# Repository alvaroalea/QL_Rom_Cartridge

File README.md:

# QL_Rom_Cartridge
Schematic, PCB and other stuff to make ROM Cartridge for use with Sinclair QL Computer

(C) 2022 Alvaro Alea Fdz.

License under: CERN Open Hardware Licence Version 2 - Strongly Reciprocal

https://ohwr.org/cern_ohl_s_v2.txt

Remenber that when using my jerber files with JLCPCB you shall mark the option to specify the Order Number (no cost) to avoid the text JLCJLCJLCJLC in the skilscreen.

## Folder: Original
This folder contain the schematic of the original Sinclair cartridge as far as i can get from pictures from internet.

It also contains 3D pieces to do vacum form of the case

STATUS
- Schematic - Working, tested and match the original, Thank You Chr$.
- Case - Design, Non tested

## Folder: Short

### NOT TESTED, SHOULD WORK
This version need a 16Kb eprom, and is intended as a replacement of Toolkit II cartridge an others.

## Folder: full_rom

### NOT TESTED, NO IDEA IF WORK
This version need a 64Kb eprom, and is intended to replace the internal ROM of the QL.

Is very important to remove the 2 ROM chips from the QL before use.

Be aware that this lock the rom cartridge, and the QL will not work without it.

## Folder: 8full_rom

### NOT TESTED, NO IDEA IF WORK
The 8full_rom is a version of full_rom with 3 switch to allow 8 diferent version of the ROM of the QL.

Is very important to remove the 2 ROM chips from the QL before use.

Be aware that this lock the rom cartridge, and the QL will not work without it.

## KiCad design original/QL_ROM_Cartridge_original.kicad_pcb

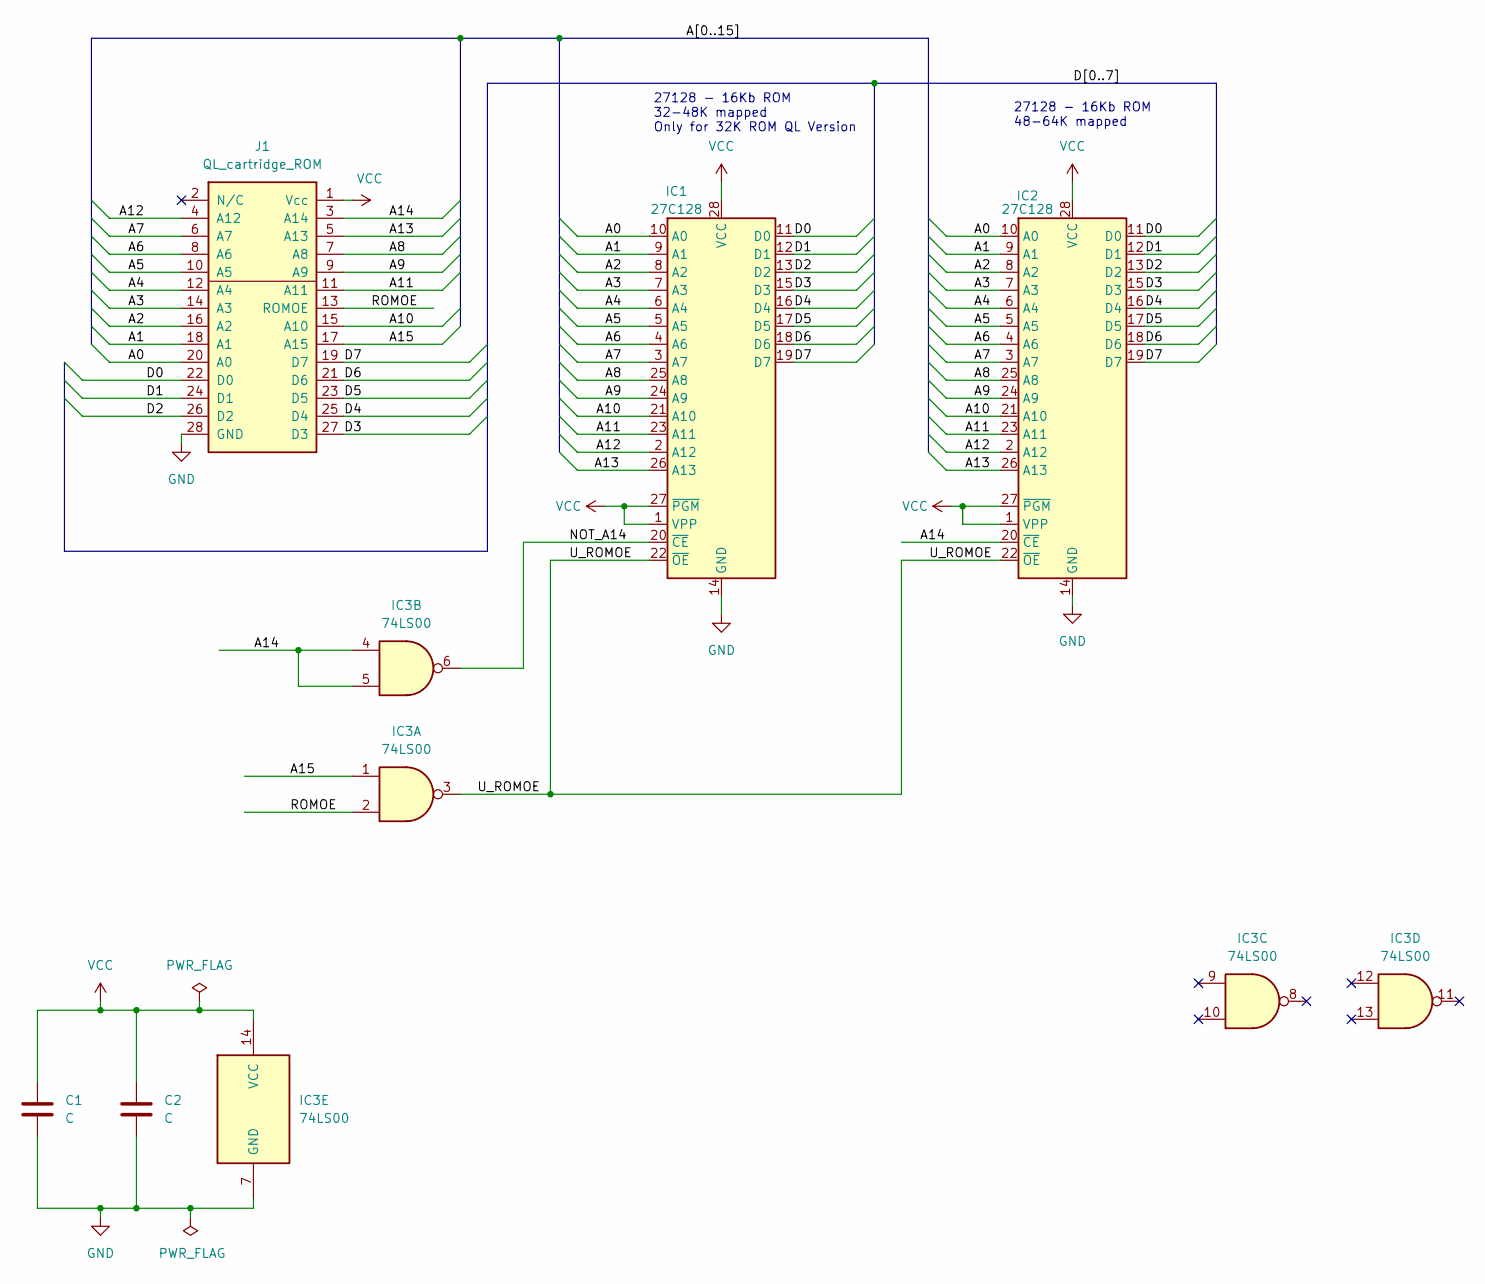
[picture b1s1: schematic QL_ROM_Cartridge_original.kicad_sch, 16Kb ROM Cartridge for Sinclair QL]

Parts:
C1: C; C_Axial_L3.8mm_D2.6mm_P12.50mm_Horizontal_Sinclair_Cartridge
C2: C; C_Axial_L3.8mm_D2.6mm_P12.50mm_Horizontal
IC1: 27C128; DIP-28_W15.24mm_sinclair_cartridge
IC2: 27C128; DIP-28_W15.24mm
IC3: 74LS00; DIP-14_W7.62mm
J1: QL_cartridge_ROM; CART_QL_EDGE

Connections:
/A0: IC1.10 (A0), IC2.10 (A0), J1.20 (A0)
/A1: IC1.9 (A1), IC2.9 (A1), J1.18 (A1)
/A2: IC1.8 (A2), IC2.8 (A2), J1.16 (A2)
/A3: IC1.7 (A3), IC2.7 (A3), J1.14 (A3)
/A4: IC1.6 (A4), IC2.6 (A4), J1.12 (A4)
/A5: IC1.5 (A5), IC2.5 (A5), J1.10 (A5)
/A6: IC1.4 (A6), IC2.4 (A6), J1.8 (A6)
/A7: IC1.3 (A7), IC2.3 (A7), J1.6 (A7)
/A8: IC1.25 (A8), IC2.25 (A8), J1.7 (A8)
/A9: IC1.24 (A9), IC2.24 (A9), J1.9 (A9)
/A10: IC1.21 (A10), IC2.21 (A10), J1.15 (A10)
/A11: IC1.23 (A11), IC2.23 (A11), J1.11 (A11)
/A12: IC1.2 (A12), IC2.2 (A12), J1.4 (A12)
/A13: IC1.26 (A13), IC2.26 (A13), J1.5 (A13)
/A14: IC2.20 (~CE), IC3.4, IC3.5, J1.3 (A14)
/A15: IC3.1, J1.17 (A15)
/D0: IC1.11 (D0), IC2.11 (D0), J1.22 (D0)
/D1: IC1.12 (D1), IC2.12 (D1), J1.24 (D1)
/D2: IC1.13 (D2), IC2.13 (D2), J1.26 (D2)
/D3: IC1.15 (D3), IC2.15 (D3), J1.27 (D3)
/D4: IC1.16 (D4), IC2.16 (D4), J1.25 (D4)
/D5: IC1.17 (D5), IC2.17 (D5), J1.23 (D5)
/D6: IC1.18 (D6), IC2.18 (D6), J1.21 (D6)
/D7: IC1.19 (D7), IC2.19 (D7), J1.19 (D7)
/NOT_A14: IC1.20 (~CE), IC3.6
/ROMOE: IC3.2, J1.13 (ROMOE)
/U_ROMOE: IC1.22 (~OE), IC2.22 (~OE), IC3.3
GND: C1.2, C2.2, IC1.14 (GND), IC2.14 (GND), IC3.7 (GND), J1.28 (GND)
VCC: C1.1, C2.1, IC1.1 (VPP), IC1.27 (~PGM), IC1.28 (VCC), IC2.1 (VPP), IC2.27 (~PGM), IC2.28 (VCC), IC3.14 (VCC), J1.1 (Vcc)

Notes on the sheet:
27128 - 16Kb ROM 32-48K mapped Only for 32K ROM QL Version
27128 - 16Kb ROM 48-64K mapped

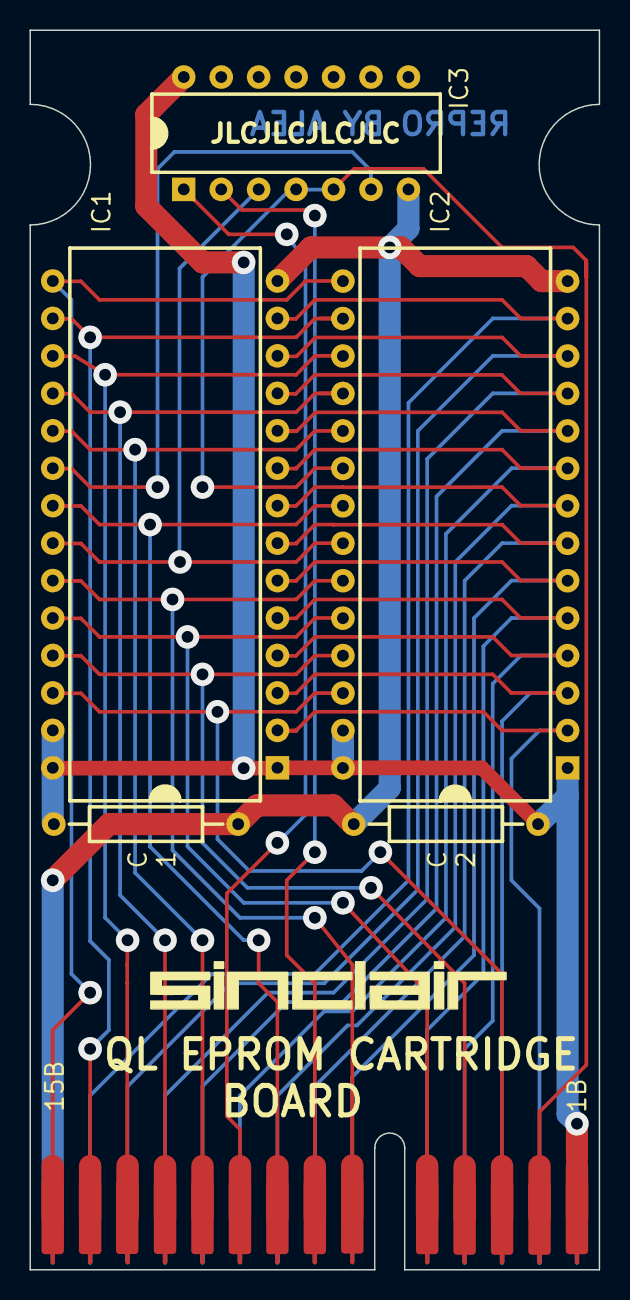
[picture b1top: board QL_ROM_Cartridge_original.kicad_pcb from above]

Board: 2 copper layers, 38.6 x 84.1 mm, 6 parts (0 on the bottom side), 29 nets.

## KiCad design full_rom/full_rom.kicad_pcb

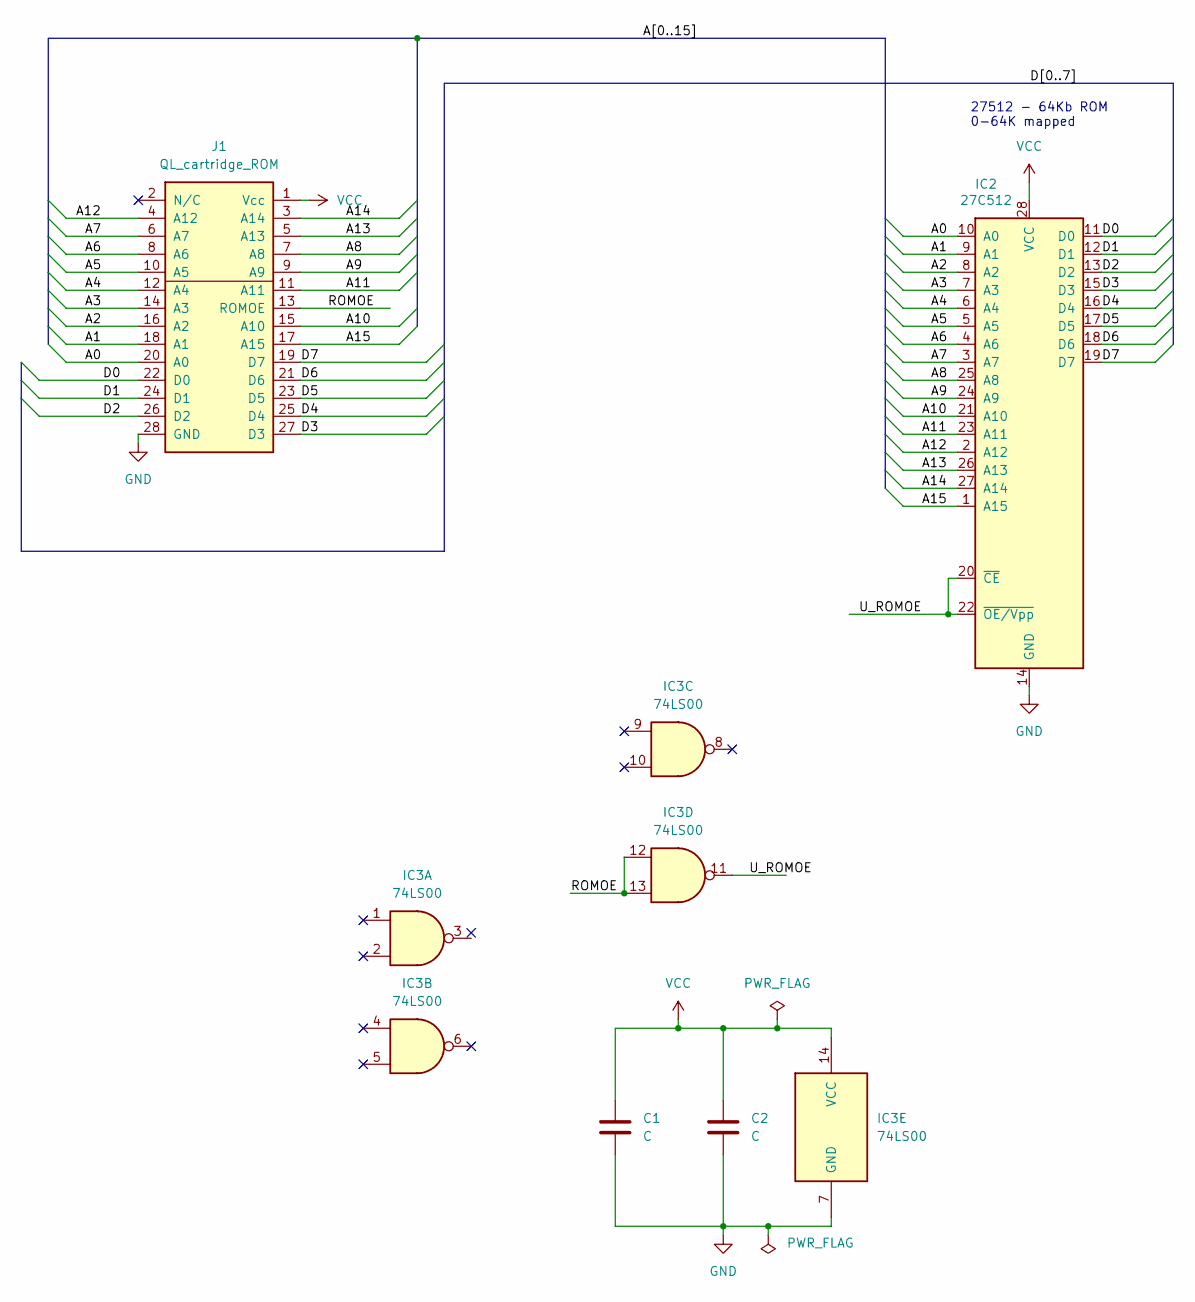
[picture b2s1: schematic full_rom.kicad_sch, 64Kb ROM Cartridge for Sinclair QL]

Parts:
C1, C2: C; C_Disc_D4.3mm_W1.9mm_P5.00mm
IC2: 27C512; DIP-28_W15.24mm
IC3: 74LS00; DIP-14_W7.62mm
J1: QL_cartridge_ROM; CART_QL_EDGE

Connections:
/A0: IC2.10 (A0), J1.20 (A0)
/A1: IC2.9 (A1), J1.18 (A1)
/A2: IC2.8 (A2), J1.16 (A2)
/A3: IC2.7 (A3), J1.14 (A3)
/A4: IC2.6 (A4), J1.12 (A4)
/A5: IC2.5 (A5), J1.10 (A5)
/A6: IC2.4 (A6), J1.8 (A6)
/A7: IC2.3 (A7), J1.6 (A7)
/A8: IC2.25 (A8), J1.7 (A8)
/A9: IC2.24 (A9), J1.9 (A9)
/A10: IC2.21 (A10), J1.15 (A10)
/A11: IC2.23 (A11), J1.11 (A11)
/A12: IC2.2 (A12), J1.4 (A12)
/A13: IC2.26 (A13), J1.5 (A13)
/A14: IC2.27 (A14), J1.3 (A14)
/A15: IC2.1 (A15), J1.17 (A15)
/D0: IC2.11 (D0), J1.22 (D0)
/D1: IC2.12 (D1), J1.24 (D1)
/D2: IC2.13 (D2), J1.26 (D2)
/D3: IC2.15 (D3), J1.27 (D3)
/D4: IC2.16 (D4), J1.25 (D4)
/D5: IC2.17 (D5), J1.23 (D5)
/D6: IC2.18 (D6), J1.21 (D6)
/D7: IC2.19 (D7), J1.19 (D7)
/ROMOE: IC3.12, IC3.13, J1.13 (ROMOE)
/U_ROMOE: IC2.20 (~CE), IC2.22 (~OE/Vpp), IC3.11
GND: C1.2, C2.2, IC2.14 (GND), IC3.7 (GND), J1.28 (GND)
VCC: C1.1, C2.1, IC2.28 (VCC), IC3.14 (VCC), J1.1 (Vcc)

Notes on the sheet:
27512 - 64Kb ROM 0-64K mapped

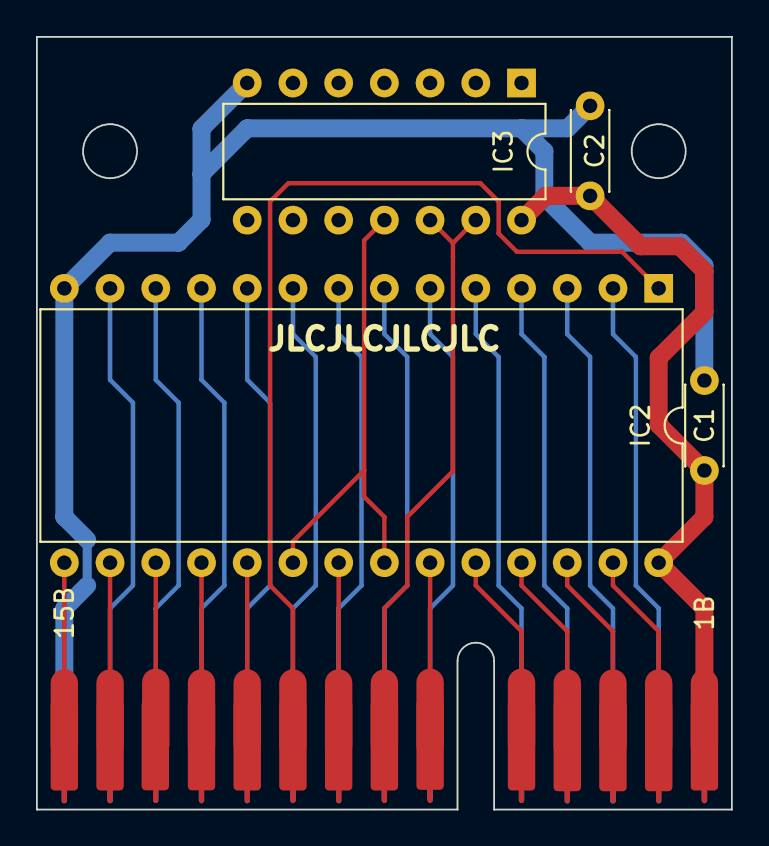
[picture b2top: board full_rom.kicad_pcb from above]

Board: 2 copper layers, 38.6 x 42.9 mm, 5 parts (0 on the bottom side), 28 nets.

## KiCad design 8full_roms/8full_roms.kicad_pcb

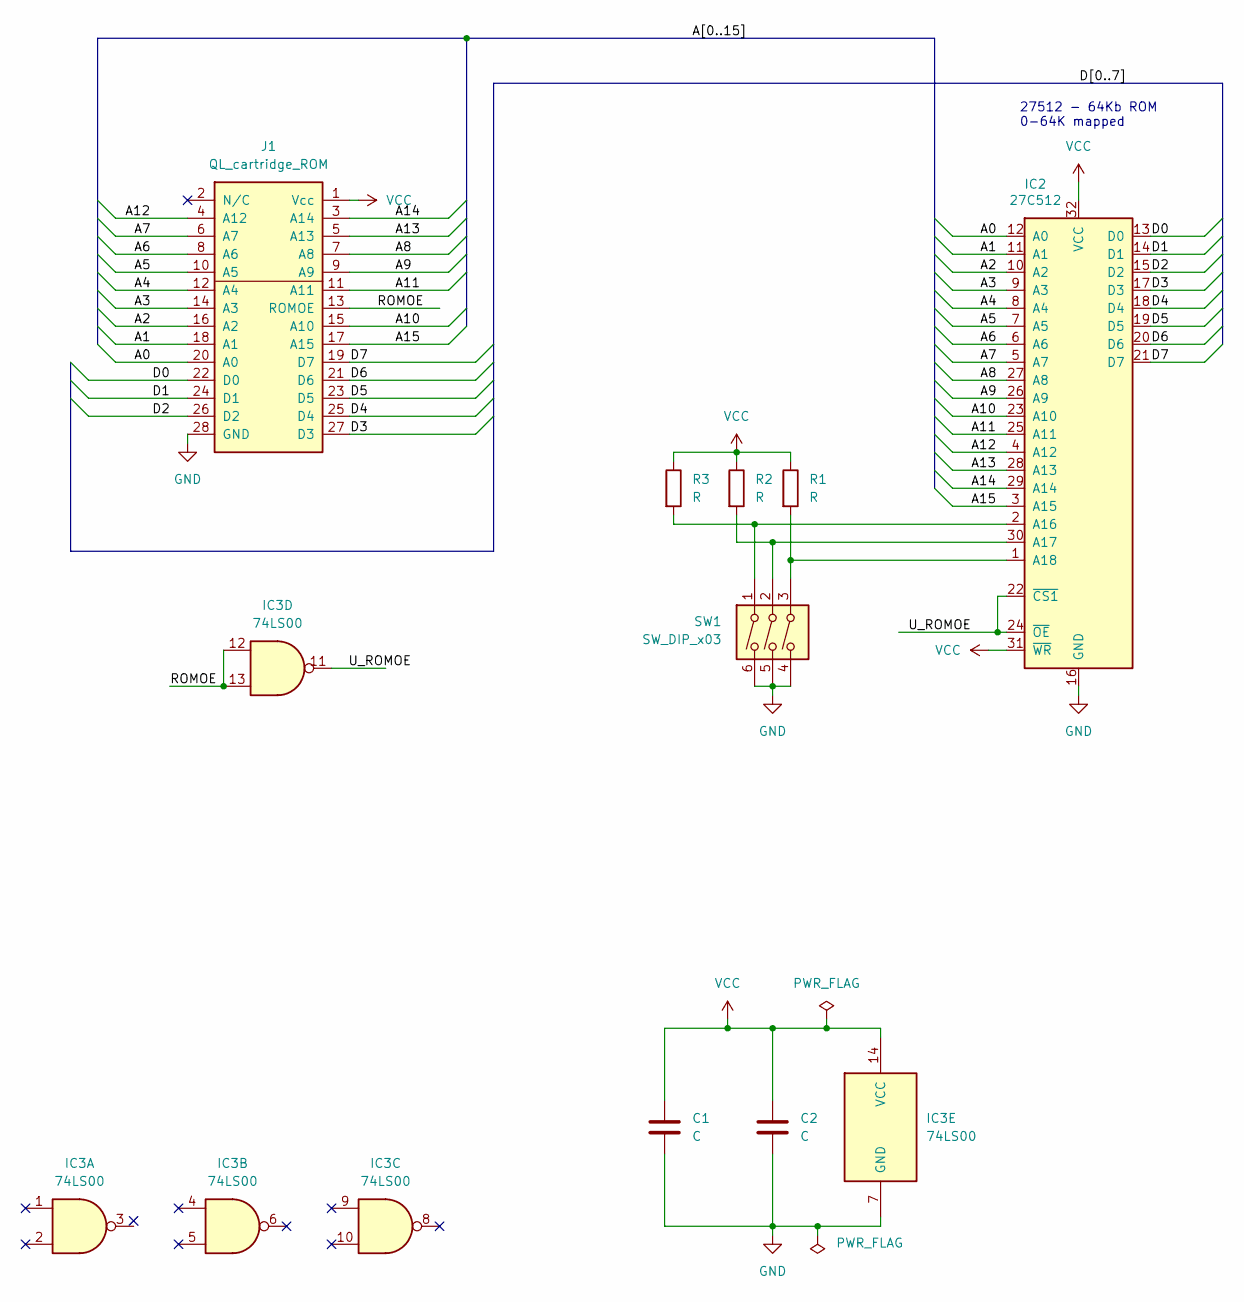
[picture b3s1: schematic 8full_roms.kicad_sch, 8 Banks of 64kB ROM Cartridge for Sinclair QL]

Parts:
C1, C2: C; C_Disc_D4.3mm_W1.9mm_P5.00mm
IC2: 27C512; DIP-32_W15.24mm_LongPads
IC3: 74LS00; DIP-14_W7.62mm
J1: QL_cartridge_ROM; CART_QL_EDGE
R1, R2, R3: R; R_Axial_DIN0204_L3.6mm_D1.6mm_P5.08mm_Horizontal
SW1: SW_DIP_x03; SW_DIP_SPSTx03_Slide_9.78x9.8mm_W7.62mm_P2.54mm

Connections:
/A0: IC2.12 (A0), J1.20 (A0)
/A1: IC2.11 (A1), J1.18 (A1)
/A2: IC2.10 (A2), J1.16 (A2)
/A3: IC2.9 (A3), J1.14 (A3)
/A4: IC2.8 (A4), J1.12 (A4)
/A5: IC2.7 (A5), J1.10 (A5)
/A6: IC2.6 (A6), J1.8 (A6)
/A7: IC2.5 (A7), J1.6 (A7)
/A8: IC2.27 (A8), J1.7 (A8)
/A9: IC2.26 (A9), J1.9 (A9)
/A10: IC2.23 (A10), J1.15 (A10)
/A11: IC2.25 (A11), J1.11 (A11)
/A12: IC2.4 (A12), J1.4 (A12)
/A13: IC2.28 (A13), J1.5 (A13)
/A14: IC2.29 (A14), J1.3 (A14)
/A15: IC2.3 (A15), J1.17 (A15)
/D0: IC2.13 (D0), J1.22 (D0)
/D1: IC2.14 (D1), J1.24 (D1)
/D2: IC2.15 (D2), J1.26 (D2)
/D3: IC2.17 (D3), J1.27 (D3)
/D4: IC2.18 (D4), J1.25 (D4)
/D5: IC2.19 (D5), J1.23 (D5)
/D6: IC2.20 (D6), J1.21 (D6)
/D7: IC2.21 (D7), J1.19 (D7)
/ROMOE: IC3.12, IC3.13, J1.13 (ROMOE)
/U_ROMOE: IC2.22 (~CS1), IC2.24 (~OE), IC3.11
GND: C1.2, C2.2, IC2.16 (GND), IC3.7 (GND), J1.28 (GND), SW1.4, SW1.5, SW1.6
unnamed: IC2.2 (A16), R3.2, SW1.1
unnamed: IC2.30 (A17), R2.2, SW1.2
unnamed: IC2.1 (A18), R1.2, SW1.3
VCC: C1.1, C2.1, IC2.31 (~WR), IC2.32 (VCC), IC3.14 (VCC), J1.1 (Vcc), R1.1, R2.1, R3.1

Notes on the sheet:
27512 - 64Kb ROM 0-64K mapped

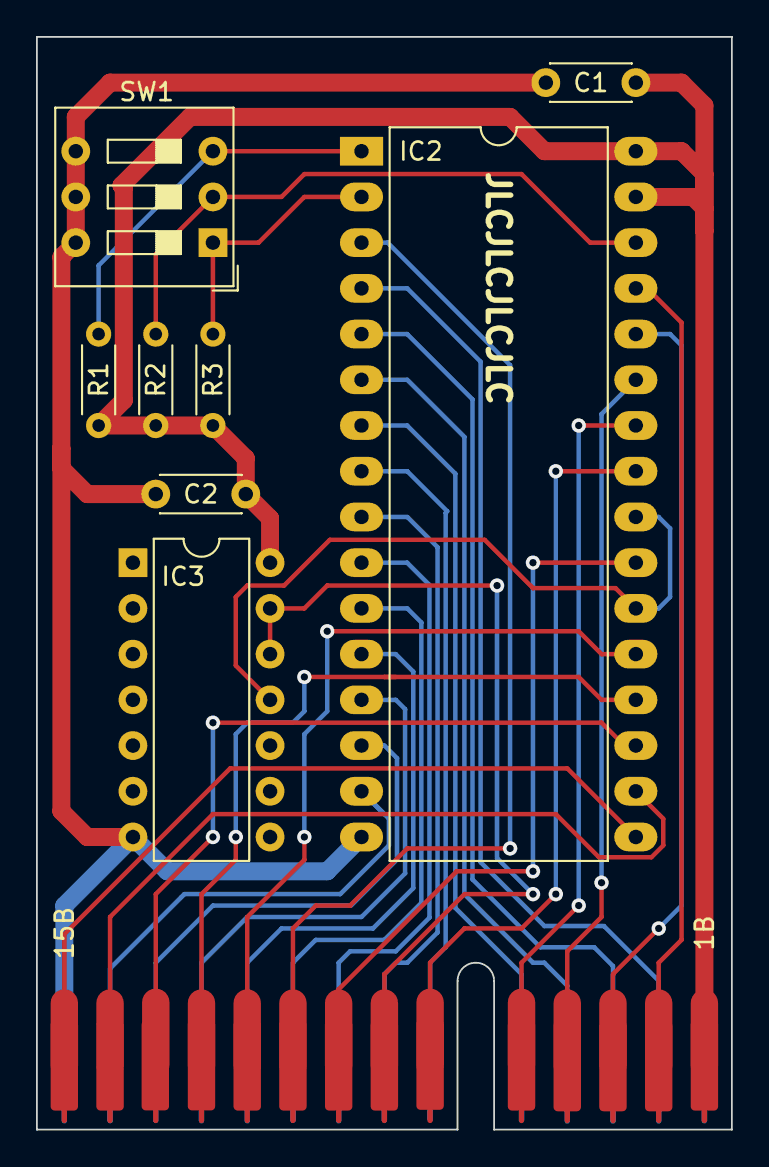
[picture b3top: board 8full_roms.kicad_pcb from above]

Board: 2 copper layers, 38.6 x 60.7 mm, 9 parts (0 on the bottom side), 31 nets.

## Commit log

2022-02-04 Initial
2022-02-04 Upload
2022-02-04 typo
2022-02-04 gerbers
2022-02-04 text updated
2022-07-15 Update size after feedback
2024-12-12 new pcbs
2025-04-24 Updated Original PCB
2025-08-04 fix gerber for 8 full roms

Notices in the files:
8full_roms/8full_roms.kicad_pcb:
Under License
(C) 2024
8full_roms/8full_roms.kicad_sch:
(c) 2024 Alvaro Alea Fdz.
